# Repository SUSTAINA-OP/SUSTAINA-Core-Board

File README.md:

<html lang="en">

<head>
	<meta charset="uft-8">
	<meta name="author" content="Masato Kubotera">
    <meta name="description" content="">
</head>

<body>
    <p><strong>This product is currently under development!</strong></p>
	<h1>SUSTAINA Core Board</h1>
        <p>
			This product is the core electronic board of the open hardware platform humanoid robot SUSTAINA-OP<sup>TM</sup>.
			This product requires multiple modules(4 x <a href="https://github.com/SUSTAINA-OP/Power-Monitor-Module">Power Monitor Module</a> and 1 x <a href="https://github.com/SUSTAINA-OP/Buck-Boost-Switch-Mode-Power-Supply-Module">Buck-Boost Switch Mode Power Supply Module</a>) to work. The board automatically selects a priority power source from two battery inputs within the operating voltage range to supply various devices. The power input and output are equipped with short-circuit protection circuits using fuses. In addition, the battery input has multiple MOSFETs to prevent reverse connection and reverse current. The power supply to the actuator and single-board computer can be turned on and off with the load switch circuit.<br>
			<br>
			Rev. 1 of this product is used by <a href="https://github.com/citbrains">CIT Brains</a>, a participant in RoboCup2023 Soccer Humanoid League KidSize.
        </p>
	<h2>Features Rev. 1</h2>
        <p>
            <table>
                <tr>
                    <th>Top Surface of PCB</th>
                    <th>Bottom Surface of PCB</th>
                    <th>Assembled Electronic Components</th>
                </tr>
                <tr>
                    <td></td>
                    <td></td>
                    <td></td>
                </tr>
            </table>
        </p>
    <h3>PCB</h3>
        <p>
            <ul>
                <li>120 mm x 70 mm PCB layout</li>
                <li>4 x ø3.5 Mounting Holes</li>
            </ul>
        </p>
	<h2>Development Environments</h2>
    <p>
        This product is designed with the following software.
            <ul>
                <li><a href="https://www.autodesk.com/products/eagle/overview">Autodesk Eagle 9.6.2</a></li>
            </ul>
    </p>
    <h2>Repository Contents</h2>
        <p>
            <dl>
                <dt><a href="/images">\images</a></dt>
                <dd>PCB preview images and capture of design screen</dd>
                <dt><a href="/libraries">\libraries</a></dt>
                <dd>Libraries used in Autodesk Eagle design</dd>
                <dt><a href="/documents">\documents</a> </dt>
                <dd>Documentation for making and using this product</dd>
                <dt><a href="/pcb_order">\pcb_order</a> </dt>
                <dd>Gerber data and documentation for ordering PCB</dd>
                <dt><a href="/schematic.pdf">schematic.pdf</a></dt>
                <dd>Circuit diagram of this product</dd>
                <dt>*.brd</dt>
                <dd>Board wiring design file by Autodesk Eagle</dd>
                <dt>*.sch</dt>
                <dd>Circuit diagram design file by Autodesk Eagle</dd>
                <dt><a href="/.gitignore">.gitignore</a></dt>
                <dd>A file that tells Git not to track a particular file</dd>
                <dt><a href="/LICENSE">LICENSE</a></dt>
                <dd>License to use this product</dd>
            </dl>
        </p>
    <h2>Documentation</h2>
        <p>
            The following documents are available for this product.
            <ul>
                <li><a href="/pcb_order/README.md">\pcb_order\README.md</a>: Information for ordering the PCB</li>
                <li><a href="/documents/BOM.md">\document\BOM.md</a>: List of electronic components assembled on the PCB</li>
            </ul>
        </p>
    <h2>References</h2>
        <p>
            This product was designed with reference to the following products.
            <ul>
                <li></li>
            </ul>
        </p>
    <h2>Contact</h2>
        <p>
            If you have any questions, please contact the designer of this product, Masato Kubodera, by <a href="mailto:masato.kubotera@sustaina-op.com">e-mail</a>.<br>
            E-mail: <a href="mailto:masato.kubotera@sustaina-op.com">masato.kubotera@sustaina-op.com</a>
        </p>
    <h2>License Information</h2>
        <p>
            This product is open source. Please review the <a href="/LICENSE">LICENSE</a> for license information.<br>
            <br>
            This product by Masato Kubotera is licensed under a <a href="http://creativecommons.org/licenses/by-nc-sa/4.0/">Creative Commons Attribution-NonCommercial-ShareAlike 4.0 International License</a>.
        </p>    
</body>
</html>

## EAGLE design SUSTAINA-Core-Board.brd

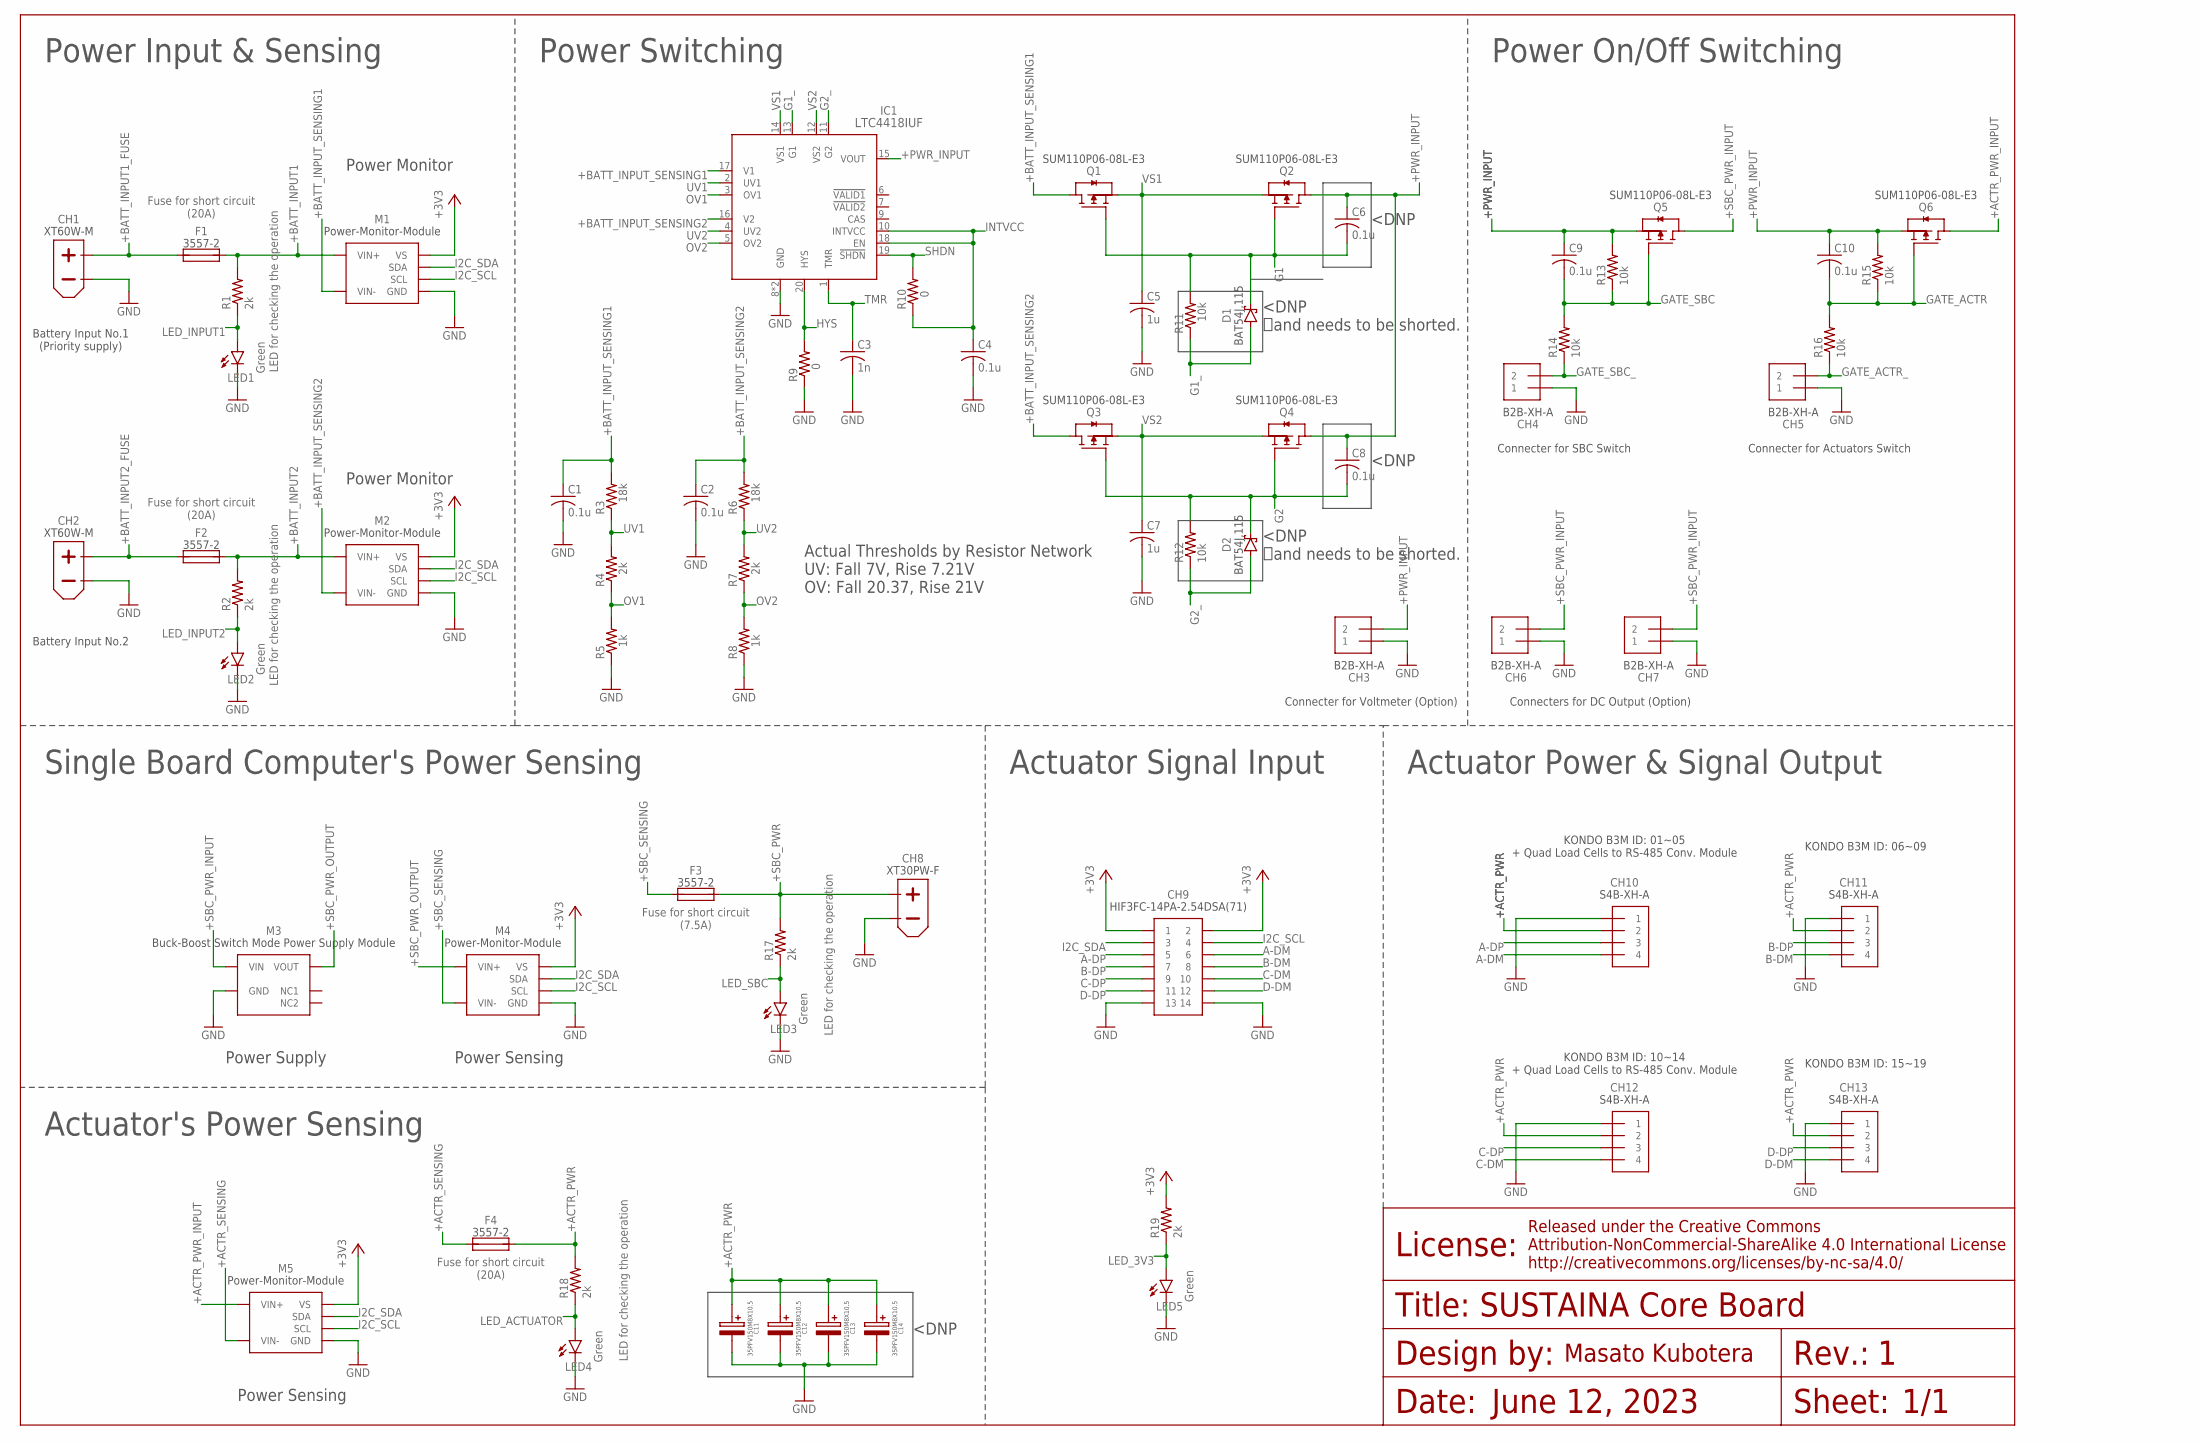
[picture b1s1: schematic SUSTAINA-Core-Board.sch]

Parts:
C1, C2, C4, C6, C8, C9, C10: 0.1u; C0603
C3: 1n; C0603
C5, C7: 1u; C0603
C11, C12, C13, C14: 35PFV150M8X10.5
CH1, CH2: XT60PW-M
CH3, CH4, CH5, CH6, CH7: B2B-XH-A
CH8: XT30PW-F
CH9: HIF3FC-14PA-2.54DSA(71)
CH10, CH11, CH12, CH13: S4B-XH-A
D1, D2: BAT54J,115; SOD-323-2
F1, F2, F3, F4: 3557-2
IC1: LTC4418IUF
LED1, LED2, LED3, LED4, LED5: Green; SML0603
M1, M2, M4, M5: POWER-MONITOR-MODULE
M3: BUCK-BOOST-SWITCH-MODE-POWER-SUPPLY-MODULE
Q1, Q2, Q3, Q4, Q5, Q6: SUM110P06-08L-E3; TO-252-3
R1, R2, R4, R7, R17, R18, R19: 2k; R0603
R3, R6: 18k; R0603
R5, R8: 1k; R0603
R9, R10: 0; R0603
R11, R12, R13, R14, R15, R16: 10k; R0603

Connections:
+3V3: CH9.1, CH9.2, M1.VS, M2.VS, M4.VS, M5.VS, R19.2
+ACTR_PWR: C11.+, C12.+, C13.+, C14.+, CH10.2, CH11.2, CH12.2, CH13.2, F4.3 (2), F4.4 (2), R18.2
+ACTR_PWR_INPUT: M5.VIN+1 (VIN+), M5.VIN+2 (VIN+), M5.VIN+3 (VIN+), M5.VIN+4 (VIN+), M5.VIN+5 (VIN+), M5.VIN+6 (VIN+), M5.VIN+7 (VIN+), M5.VIN+8 (VIN+), M5.VIN+9 (VIN+), M5.VIN+10 (VIN+), Q6.4 (D)
+ACTR_SENSING: F4.1, F4.2 (1), M5.VIN-1 (VIN-), M5.VIN-2 (VIN-), M5.VIN-3 (VIN-), M5.VIN-4 (VIN-), M5.VIN-5 (VIN-), M5.VIN-6 (VIN-), M5.VIN-7 (VIN-), M5.VIN-8 (VIN-), M5.VIN-9 (VIN-), M5.VIN-10 (VIN-)
+BATT_INPUT1: F1.3 (2), F1.4 (2), M1.VIN+1 (VIN+), M1.VIN+2 (VIN+), M1.VIN+3 (VIN+), M1.VIN+4 (VIN+), M1.VIN+5 (VIN+), M1.VIN+6 (VIN+), M1.VIN+7 (VIN+), M1.VIN+8 (VIN+), M1.VIN+9 (VIN+), M1.VIN+10 (VIN+), R1.2
+BATT_INPUT1_FUSE: CH1.+, F1.1, F1.2 (1)
+BATT_INPUT2: F2.3 (2), F2.4 (2), M2.VIN+1 (VIN+), M2.VIN+2 (VIN+), M2.VIN+3 (VIN+), M2.VIN+4 (VIN+), M2.VIN+5 (VIN+), M2.VIN+6 (VIN+), M2.VIN+7 (VIN+), M2.VIN+8 (VIN+), M2.VIN+9 (VIN+), M2.VIN+10 (VIN+), R2.2
+BATT_INPUT2_FUSE: CH2.+, F2.1, F2.2 (1)
+BATT_INPUT_SENSING1: C1.1, IC1.17 (V1), M1.VIN-1 (VIN-), M1.VIN-2 (VIN-), M1.VIN-3 (VIN-), M1.VIN-4 (VIN-), M1.VIN-5 (VIN-), M1.VIN-6 (VIN-), M1.VIN-7 (VIN-), M1.VIN-8 (VIN-), M1.VIN-9 (VIN-), M1.VIN-10 (VIN-), Q1.4 (D), R3.2
+BATT_INPUT_SENSING2: C2.1, IC1.16 (V2), M2.VIN-1 (VIN-), M2.VIN-2 (VIN-), M2.VIN-3 (VIN-), M2.VIN-4 (VIN-), M2.VIN-5 (VIN-), M2.VIN-6 (VIN-), M2.VIN-7 (VIN-), M2.VIN-8 (VIN-), M2.VIN-9 (VIN-), M2.VIN-10 (VIN-), Q3.4 (D), R6.2
+PWR_INPUT: C6.1, C8.1, C9.1, C10.1, CH3.2, IC1.15 (VOUT), Q2.4 (D), Q4.4 (D), Q5.3 (S), Q6.3 (S), R13.2, R15.2
+SBC_PWR: CH8.+, F3.3 (2), F3.4 (2), R17.2
+SBC_PWR_INPUT: CH6.2, CH7.2, M3.VIN1 (VIN), M3.VIN2 (VIN), M3.VIN3 (VIN), Q5.4 (D)
+SBC_PWR_OUTPUT: M3.VOUT1 (VOUT), M3.VOUT2 (VOUT), M3.VOUT3 (VOUT), M4.VIN+1 (VIN+), M4.VIN+2 (VIN+), M4.VIN+3 (VIN+), M4.VIN+4 (VIN+), M4.VIN+5 (VIN+), M4.VIN+6 (VIN+), M4.VIN+7 (VIN+), M4.VIN+8 (VIN+), M4.VIN+9 (VIN+), M4.VIN+10 (VIN+)
+SBC_SENSING: F3.1, F3.2 (1), M4.VIN-1 (VIN-), M4.VIN-2 (VIN-), M4.VIN-3 (VIN-), M4.VIN-4 (VIN-), M4.VIN-5 (VIN-), M4.VIN-6 (VIN-), M4.VIN-7 (VIN-), M4.VIN-8 (VIN-), M4.VIN-9 (VIN-), M4.VIN-10 (VIN-)
A-DM: CH9.6, CH10.4
A-DP: CH9.5, CH10.3
B-DM: CH9.8, CH11.4
B-DP: CH9.7, CH11.3
C-DM: CH9.10, CH12.4
C-DP: CH9.9, CH12.3
D-DM: CH9.12, CH13.4
D-DP: CH9.11, CH13.3
G1: C6.2, D1.1 (C), Q1.1 (G), Q2.1 (G), R11.2
G1_: D1.2 (A), IC1.13 (G1), R11.1
G2: C8.2, D2.1 (C), Q3.1 (G), Q4.1 (G), R12.2
G2_: D2.2 (A), IC1.11 (G2), R12.1
GATE_ACTR: C10.2, Q6.1 (G), R15.1, R16.2
GATE_ACTR_: CH5.2, R16.1
GATE_SBC: C9.2, Q5.1 (G), R13.1, R14.2
GATE_SBC_: CH4.2, R14.1
GND: C1.2, C2.2, C3.2, C4.2, C5.2, C7.2, C11.-, C12.-, C13.-, C14.-, CH1.-, CH2.-, CH3.1, CH4.1, CH5.1, CH6.1, CH7.1, CH8.-, CH9.13, CH9.14, CH10.1, CH11.1, CH12.1, CH13.1, IC1.8 (GND), IC1.21 (GND), LED1.C, LED2.C, LED3.C, LED4.C, LED5.C, M1.GND, M2.GND, M3.GND1 (GND), M3.GND2 (GND), M3.GND3 (GND), M3.GND4 (GND), M3.GND5 (GND), M3.GND6 (GND), M4.GND, M5.GND, R5.1, R8.1, R9.1
HYS: IC1.20 (HYS), R9.2
I2C_SCL: CH9.4, M1.SCL, M2.SCL, M4.SCL, M5.SCL
I2C_SDA: CH9.3, M1.SDA, M2.SDA, M4.SDA, M5.SDA
INTVCC: C4.1, IC1.10 (INTVCC), IC1.18 (EN), R10.1
LED_3V3: LED5.A, R19.1
LED_ACTUATOR: LED4.A, R18.1
LED_INPUT1: LED1.A, R1.1
LED_INPUT2: LED2.A, R2.1
LED_SBC: LED3.A, R17.1
OV1: IC1.3 (OV1), R4.1, R5.2
OV2: IC1.5 (OV2), R7.1, R8.2
SHDN: IC1.19 (!SHDN), R10.2
TMR: C3.1, IC1.1 (TMR)
UV1: IC1.2 (UV1), R3.1, R4.2
UV2: IC1.4 (UV2), R6.1, R7.2
VS1: C5.1, IC1.14 (VS1), Q1.3 (S), Q2.3 (S)
VS2: C7.1, IC1.12 (VS2), Q3.3 (S), Q4.3 (S)

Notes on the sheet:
Connecter for SBC Switch
Battery Input No.1 (Priority supply)
LED for checking the operation
Fuse for short circuit (7.5A)
Fuse for short circuit (20A)
KONDO B3M ID: 01~05 + Quad Load Cells to RS-485 Conv. Module
Connecter for Actuators Switch
KONDO B3M ID: 06~09
KONDO B3M ID: 10~14 + Quad Load Cells to RS-485 Conv. Module
KONDO B3M ID: 15~19
Battery Input No.2
Connecters for DC Output (Option)
Connecter for Voltmeter (Option)
1/1
June 12, 2023
SUSTAINA Core Board
Power Input & Sensing
Power Switching
Power Monitor
Power On/Off Switching
Actuator Power & Signal Output
Actuator Signal Input
Single Board Computer's Power Sensing
Actuator's Power Sensing
Power Supply
Power Sensing
<DNP and needs to be shorted.
<DNP
Actual Thresholds by Resistor Network UV: Fall 7V, Rise 7.21V OV: Fall 20.37, Rise 21V

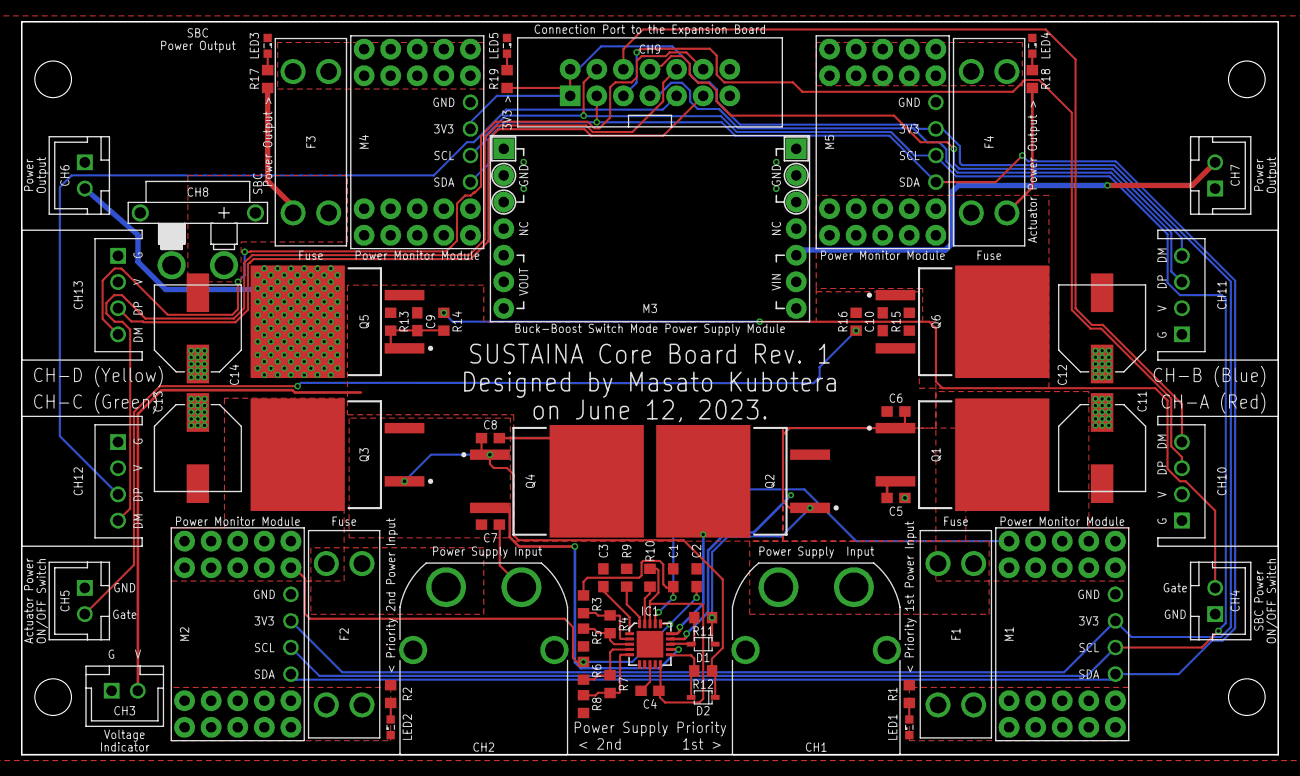
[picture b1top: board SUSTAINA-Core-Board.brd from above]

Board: 2 copper layers, 120.0 x 70.0 mm, 69 parts (0 on the bottom side), 49 nets.

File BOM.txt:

Qty Value                                      Device                                     Package                                    Parts                        Description                
2   0                                          R-US_R0603                                 R0603                                      R9, R10                      RESISTOR, American symbol  
7   0.1u                                       C-USC0603                                  C0603                                      C1, C2, C4, C5, C6, C7, C8   CAPACITOR, American symbol 
6   10k                                        R-US_R0603                                 R0603                                      R11, R12, R13, R14, R15, R16 RESISTOR, American symbol  
2   1180k                                      R-US_R0603                                 R0603                                      R3, R6                       RESISTOR, American symbol  
1   1n                                         C-USC0603                                  C0603                                      C3                           CAPACITOR, American symbol 
2   1u                                         C-USC0603                                  C0603                                      C9, C10                      CAPACITOR, American symbol 
5   2k                                         R-US_R0603                                 R0603                                      R1, R2, R17, R18, R19        RESISTOR, American symbol  
2   34k                                        R-US_R0603                                 R0603                                      R4, R7                       RESISTOR, American symbol  
4   3557-2                                     3557-2                                     3557-2                                     F1, F2, F3, F4                                          
4   35PFV150M8X10.5                            35PFV150M8X10.5                            35PFV150M8X10.5                            C11, C12, C13, C14                                      
2   86.6k                                      R-US_R0603                                 R0603                                      R5, R8                       RESISTOR, American symbol  
5   B2B-XH-A                                   B2B-XH-A                                   B2B-XH-A                                   CH3, CH4, CH5, CH6, CH7                                 
2   BAT54J,115                                 BAT54J,115                                 SOD-323-2                                  D1, D2                                                  
1   BUCK-BOOST-SWITCH-MODE-POWER-SUPPLY-MODULE BUCK-BOOST-SWITCH-MODE-POWER-SUPPLY-MODULE BUCK-BOOST-SWITCH-MODE-POWER-SUPPLY-MODULE M3                                                      
5   Green                                      LEDSML0603                                 SML0603                                    LED1, LED2, LED3, LED4, LED5 LED                        
1   HIF3FC-14PA-2.54DSA(71)                    HIF3FC-14PA-2.54DSA(71)                    HIF3FC-14PA-2.54DSA(71)                    CH9                                                     
1   LTC4418IUF                                 LTC4418IUF                                 LTC4418IUF                                 IC1                                                     
4   POWER-MONITOR-MODULE                       POWER-MONITOR-MODULE                       POWER-MONITOR-MODULE                       M1, M2, M4, M5                                          
4   S4B-XH-A                                   S4B-XH-A                                   S4B-XH-A                                   CH10, CH11, CH12, CH13                                  
6   SUM110P06-08L-E3                           SUM110P06-08L-E3                           TO-252-3                                   Q1, Q2, Q3, Q4, Q5, Q6                                  
1   XT30PW-F                                   XT30PW-F                                   XT30PW-F                                   CH8                                                     
2   XT60PW-M                                   XT60PW-M                                   XT60PW-M                                   CH1, CH2

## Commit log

2023-06-07 Initial upload
2023-06-07 Minimum net thickness changed from 5mil to 8mil
2023-06-20 Changed board color (Rev 1, 1st order specification)
2023-07-25 Upload data for RoboCup2023 competition specifications
2023-07-30 Added sample programs for multiple voltage and current measurements using Arduino
2023-09-13 Solved the problem of not being able to use a switching power supply in Rev.1
2023-09-13 Changed the version of schematic to 1.1

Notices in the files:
parts and their libraries:
Frames: Released under the Creative Commons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
